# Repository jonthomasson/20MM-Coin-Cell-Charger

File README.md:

# 20MM-Coin-Cell-Charger
USB based coin cell charger for 2016, 2020, 2025, 2032

This is a very small and affordable lithium coin cell charger. It'll charge several 20mm type coin cell batteries. Total BOM for me was $2 for one. I picked up 3 boards from oshpark for $7.70. The PCB is available to order from the oshpark links below. All files, including BOM to reproduce this project have been included and linked to in my github repository. 

I had the need for an LIR2032 coin cell charger to power a few projects. Unfortunately (or fortunately depending on how you look at it) , the charger I had ordered off Amazon didn't work, so I decided to build my own.

I took the guts of the Solder Sniffer 9000 project, which consisted of an MCP73831 for the charge controller, and modified it a bit to charge an LIR2032.

The main change needed was the value of R3, which is responsible for setting the max charge current. For the LIR2032, the max charge current is 35mA. By using the supplied formula in the MCP73831 datasheet (I = 1000V/R) I was able to find that a 28K resistor would give me the charge current needed. To get a decent connection to the USB socket, I tinned each of the pads a bit.

The value of R3 can be adjusted from anywhere between 28K and 67K. Of course, the higher the resistor, the less charge current and thus the longer the battery will take to charge. 

I wanted the charger to be as compact and simple as possible. For this reason I chose to create the USB plug out of the PCB to save on cost. I also shrank the total footprint of the board to just a little wider than the coin cell holder. 

![enter image description here](https://lh3.googleusercontent.com/uD5Zvyg85dlW-8f5IwnGq1qh3priR2OKTf4Tjj70FocnqzpL80pZEwNxS6ZUOIJZ3bOK8rinoLwqm-kq8-yH0MLIolsSJiKuncZRWuq5fff_9x6JYAw69AOmUJirfUg54P8FFv8bwBKHHiX_kHhZIYlRzVH4VCt6vmoh7Wrd-KqcxMrddQk4-25mwzTWE0iW7ZNwNjoGs3RwSbsidzb3QryAKgb_yxtJhBo4KMirsXQbsdFOMZq7Y3z6rZIYUdM-XyfDFbPD5xv3zA5LSqq2kRc23ahrXRyeBDxgmhGTQgWLqGTcRTgCgeo8IFCQZkKFoeolskZmo0prZTthkYjzgXvv5mR0HkPeojK2pc00fEuveZ6zjvWLD1UQeqiW7-IDgYX7loi24kw2VcKIAagTxrQj6foRBIVHi2muKb2Pi6O9z38uYJrBgjTunJksEoWYleK08SUY6MwBFgLk_1BG-RDB7DysfZfV7GayoazVCK2zVVLhoKfka0t-n1q-EDSQCePSgshjR7F-HWpJjVMxTcRX2fhKbYLuZ5pw_itjAjXo3ic1X2LXyL-f9xo5TAUJtNLcjCi2JJOBEcFjj4XJYrKz78IaFwwrERfT8UP-=w1688-h949-no)

![enter image description here](https://lh3.googleusercontent.com/PXCVL6h58zrs98nUhsCSNDjTJsKGtNxcaz6ifn4IY02xm1BFlol4Sx9Q6Okw4b5Lm4KdBB9pGmgYVPm0FkVdIyBvV0Q52LWY7phe2oq7p3IzxVEZNmcpIT2coyVlEAW5EqwGsNqAhrx_Q4ajqmGU5bltQAeT0Fgz96oerCWiQvKgs8LsBqb7jo2Qsm4JUMKcDapJaEEI7Ur0PlGySvpDgjmAqNowEZRN4vlKlrdvWe55Qx3N-yrDrYwRpyWHOdIcLfOoiHE2GyEJ-LVXT2m8K6H7Jowp1JbvCEUAa7eoxudCDMmjdhb6d9VDzz6i_ksSDXJBoXndn32iHg4le24-qd6Cu8ZIrL_ebzEqwR0eW30USKSWrRg9-CR6mxuRMoZPQnY16-aC-Hgn_BDKasSCstxdyoZmfaA2ZwAKz8K7MUG-PuzbrlVb5urmvWEqTZ9Fw8scGtUB1AcNSU7m2DHWh5EWR4FkH9jx8OCoFD5EQoh2zMfmDwgAyex-1bCETqFs2LDvDGdbV5F1-HuWiNDIWk1G8Mb6xdKH6Id_z4F4L-VYAyaA4Hc89aNqZIccZkhBwxmpKzNps0qzLUKnWn5UBtzh6oon4NoOldWxC6ZK=w1079-h607-no)

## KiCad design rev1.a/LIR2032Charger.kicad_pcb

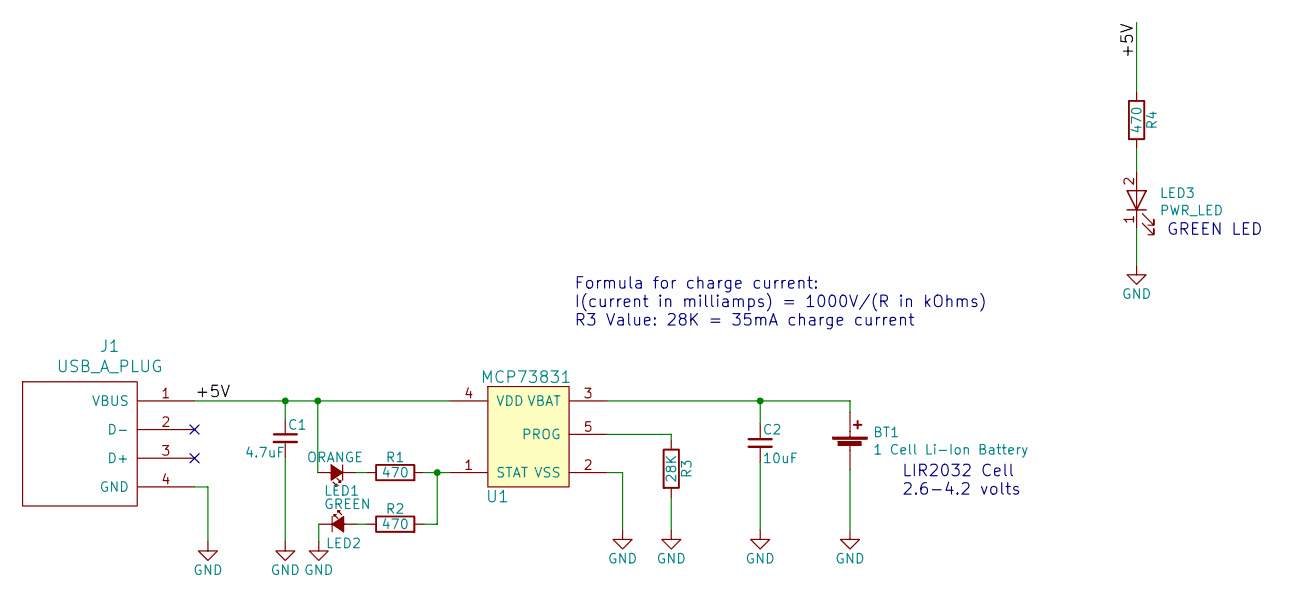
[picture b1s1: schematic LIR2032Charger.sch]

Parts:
BT1: 1 Cell Li-Ion Battery; BatteryHolder_MPD_BK_888
C1: 4.7uF; C_0805
C2: 10uF; C_1206
J1: USB_A_PLUG; usb-PCB
LED1: ORANGE; LED_0805
LED2: GREEN; LED_0805
LED3: PWR_LED; LED_0805
R1, R2, R4: 470; R_0805
R3: 28K; R_0805
U1: MCP73831; Microchip_MCP73831

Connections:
/+5V: C1.1, J1.1 (VBUS), LED1.2 (A), R4.1, U1.4 (VDD)
GND: BT1.2 (-), C1.2, C2.2, J1.4 (GND), LED2.1 (K), LED3.1 (K), R3.2, U1.2 (VSS)
unnamed: BT1.1 (+), C2.1, U1.3 (VBAT)
unnamed: LED1.1 (K), R1.1
unnamed: LED2.2 (A), R2.1
unnamed: LED3.2 (A), R4.2
unnamed: R1.2, R2.2, U1.1 (STAT)
unnamed: R3.1, U1.5 (PROG)

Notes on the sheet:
GREEN LED
Formula for charge current: I(current in milliamps) = 1000V/(R in kOhms) R3 Value: 28K = 35mA charge current
LIR2032 Cell 2.6-4.2 volts

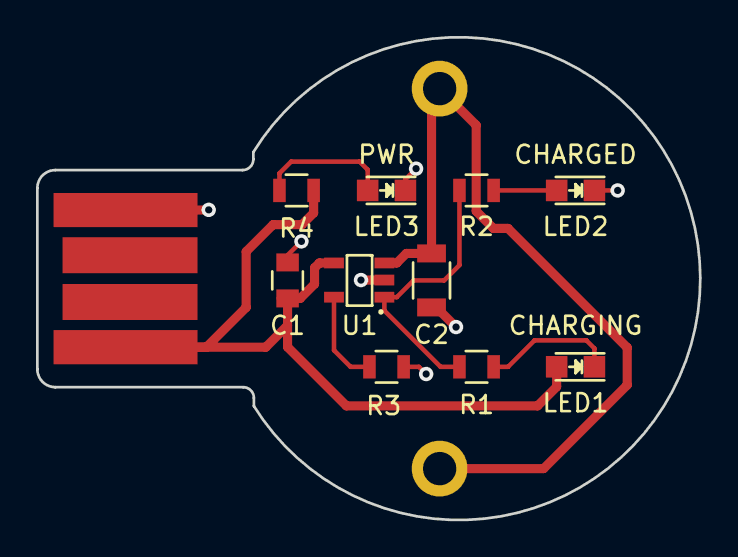
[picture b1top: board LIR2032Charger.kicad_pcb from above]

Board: 2 copper layers, 36.8 x 26.8 mm, 12 parts (1 on the bottom side), 8 nets.

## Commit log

2017-07-10 :space_invader: Added .gitattributes & .gitignore files
2017-07-10 initial checkin
2017-09-24 fixed erc errors and added gerber files
